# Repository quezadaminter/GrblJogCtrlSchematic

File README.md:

# GrblJogCtrlSchematic
Schematic for the embedded GRBL jog controller.  

This is in the form of a KiCAD project.  

The microcontroller board used (Teensy 4.1): https://www.pjrc.com/store/teensy41.html  

The Display breakout board called out in the schematic can be ordered from OshPark: https://oshpark.com/shared_projects/ZNeN5t92  
The TFT LCD I used is from BuyDisplay.com: https://www.buydisplay.com/serial-spi-3-5-inch-tft-lcd-module-in-320x480-optl-touchscreen-ili9488  

I have no affiliation with BuyDislay.com or PJRC.  

Write up about the device with pictures and links to demo videos: https://discuss.inventables.com/t/grbl-hand-held-controller-with-jog-wheel-dro-and-built-in-sender/109009  

Source code for the Teensy 4.1: https://github.com/quezadaminter/GrblJogCtrl  

# Page 1/3

# Page 2/3

# Page 3/3

# Parts Used
1- Teensy 4.1 Development Board.  
1- ILI9488 LCD https://www.buydisplay.com/serial-spi-3-5-inch-tft-lcd-module-in-320x480-optl-touchscreen-ili9488  
1- 50 pin LCD breakout adapter board. Link in the schematic.  
1- 12 Button key pad, I made my own but there are many options out there.  
1- Shift register IC to read keypad.  
2- 12 position rotary selector switches (12PST).  
1- Female USB 2.0 type A connector.  
1- 20 pulse rotary encoder with momentary switch. Feel free to substitute for one with a higher resolution.

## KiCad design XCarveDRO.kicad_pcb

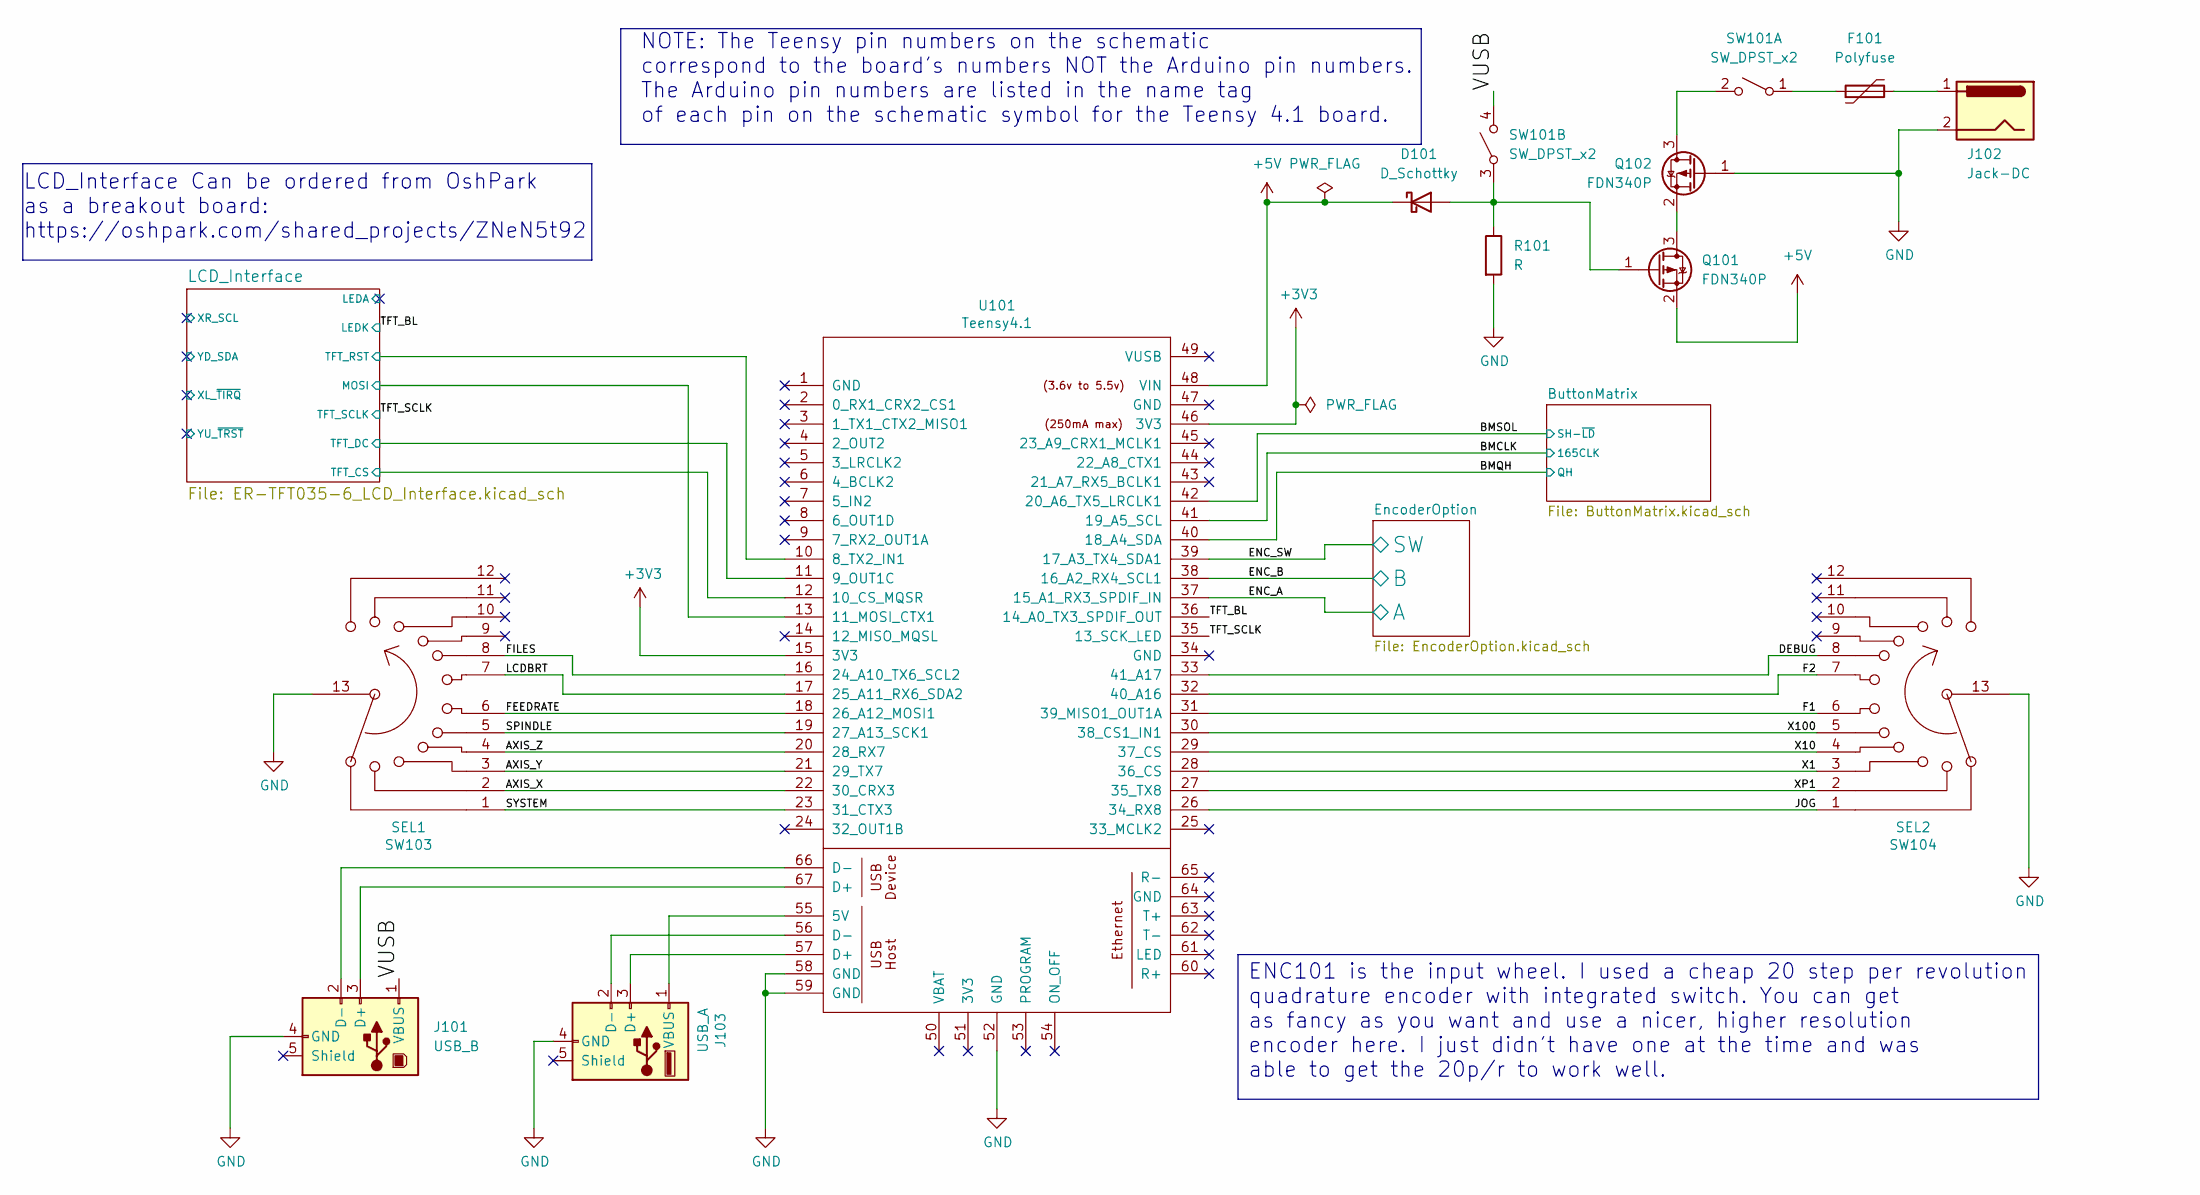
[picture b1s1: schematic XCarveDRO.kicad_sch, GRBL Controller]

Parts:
D101: D_Schottky; D_SOD-323_HandSoldering
F101: Polyfuse; Fuse_1210_3225Metric_Pad1.42x2.65mm_HandSolder
J101: USB_B; USB_B_Lumberg_2411_02_Horizontal
J102: Jack-DC; PinHeader_1x02_P2.54mm_Vertical
J103: USB_A; USB_A_Stewart_SS-52100-001_Horizontal
Q101, Q102: FDN340P; SOT-23
R101: R; R_0805_2012Metric_Pad1.20x1.40mm_HandSolder
SW101: SW_DPST_x2; PinHeader_1x04_P2.54mm_Vertical
SW103: SEL1; SWITCH_ROTARY_4-12-No_Cuts
SW104: SEL2; SWITCH_ROTARY_4-12-No_Cuts
U101: Teensy4.1; Teensy41

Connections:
+5V: D101.1 (K), Q101.2 (S), U101.48 (VIN)
/AXIS_X: SW103.2, U101.22 (30_CRX3)
/AXIS_Y: SW103.3, U101.21 (29_TX7)
/AXIS_Z: SW103.4, U101.20 (28_RX7)
/BMCLK: U101.41 (19_A5_SCL); also elsewhere on the board
/BMQH: U101.40 (18_A4_SDA); also elsewhere on the board
/BMSOL: U101.42 (20_A6_TX5_LRCLK1); also elsewhere on the board
/DEBUG: SW104.8, U101.33 (41_A17)
/ENC_A: U101.37 (15_A1_RX3_SPDIF_IN); also elsewhere on the board
/ENC_B: U101.38 (16_A2_RX4_SCL1); also elsewhere on the board
/ENC_SW: U101.39 (17_A3_TX4_SDA1); also elsewhere on the board
/F1: SW104.6, U101.31 (39_MISO1_OUT1A)
/F2: SW104.7, U101.32 (40_A16)
/FEEDRATE: SW103.6, U101.18 (26_A12_MOSI1)
/FILES: SW103.8, U101.16 (24_A10_TX6_SCL2)
/JOG: SW104.1, U101.26 (34_RX8)
/LCDBRT: SW103.7, U101.17 (25_A11_RX6_SDA2)
/LCD_Interface/MOSI: U101.13 (11_MOSI_CTX1); also elsewhere on the board
/LCD_Interface/TFT_CS: U101.12 (10_CS_MQSR); also elsewhere on the board
/LCD_Interface/TFT_DC: U101.11 (9_OUT1C); also elsewhere on the board
/LCD_Interface/TFT_RST: U101.10 (8_TX2_IN1); also elsewhere on the board
/SPINDLE: SW103.5, U101.19 (27_A13_SCK1)
/SYSTEM: SW103.1, U101.23 (31_CTX3)
/TFT_BL: U101.36 (14_A0_TX3_SPDIF_OUT); also elsewhere on the board
/TFT_SCLK: U101.35 (13_SCK_LED); also elsewhere on the board
/VUSB: J101.1 (VBUS), SW101.4 (B)
/X1: SW104.3, U101.28 (36_CS)
/X10: SW104.4, U101.29 (37_CS)
/X100: SW104.5, U101.30 (38_CS1_IN1)
/XP1: SW104.2, U101.27 (35_TX8)
GND: J101.4 (GND), J102.2, J103.4 (GND), Q102.1 (G), R101.2, SW103.13, SW104.13, U101.52 (GND), U101.58 (GND), U101.59 (GND); also elsewhere on the board
unnamed: D101.2 (A), Q101.1 (G), R101.1, SW101.3 (A)
unnamed: F101.1, SW101.1 (A)
unnamed: F101.2, J102.1
unnamed: J101.2 (D-), U101.66 (D-)
unnamed: J101.3 (D+), U101.67 (D+)
unnamed: J103.1 (VBUS), U101.55 (5V)
unnamed: J103.2 (D-), U101.56 (D-)
unnamed: J103.3 (D+), U101.57 (D+)
unnamed: Q101.3 (D), Q102.2 (S)
unnamed: Q102.3 (D), SW101.2 (B)

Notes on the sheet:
LCD_Interface Can be ordered from OshPark as a breakout board: https://oshpark.com/shared_projects/ZNeN5t92
NOTE: The Teensy pin numbers on the schematic correspond to the board's numbers NOT the Arduino pin numbers. The Arduino pin numbers are listed in the name tag of each pin on the schematic symbol for the Teensy 4.1 board.
ENC101 is the input wheel. I used a cheap 20 step per revolution quadrature encoder with integrated switch. You can get as fancy as you want and use a nicer, higher resolution encoder here. I just didn't have one at the time and was able to get the 20p/r to work well.

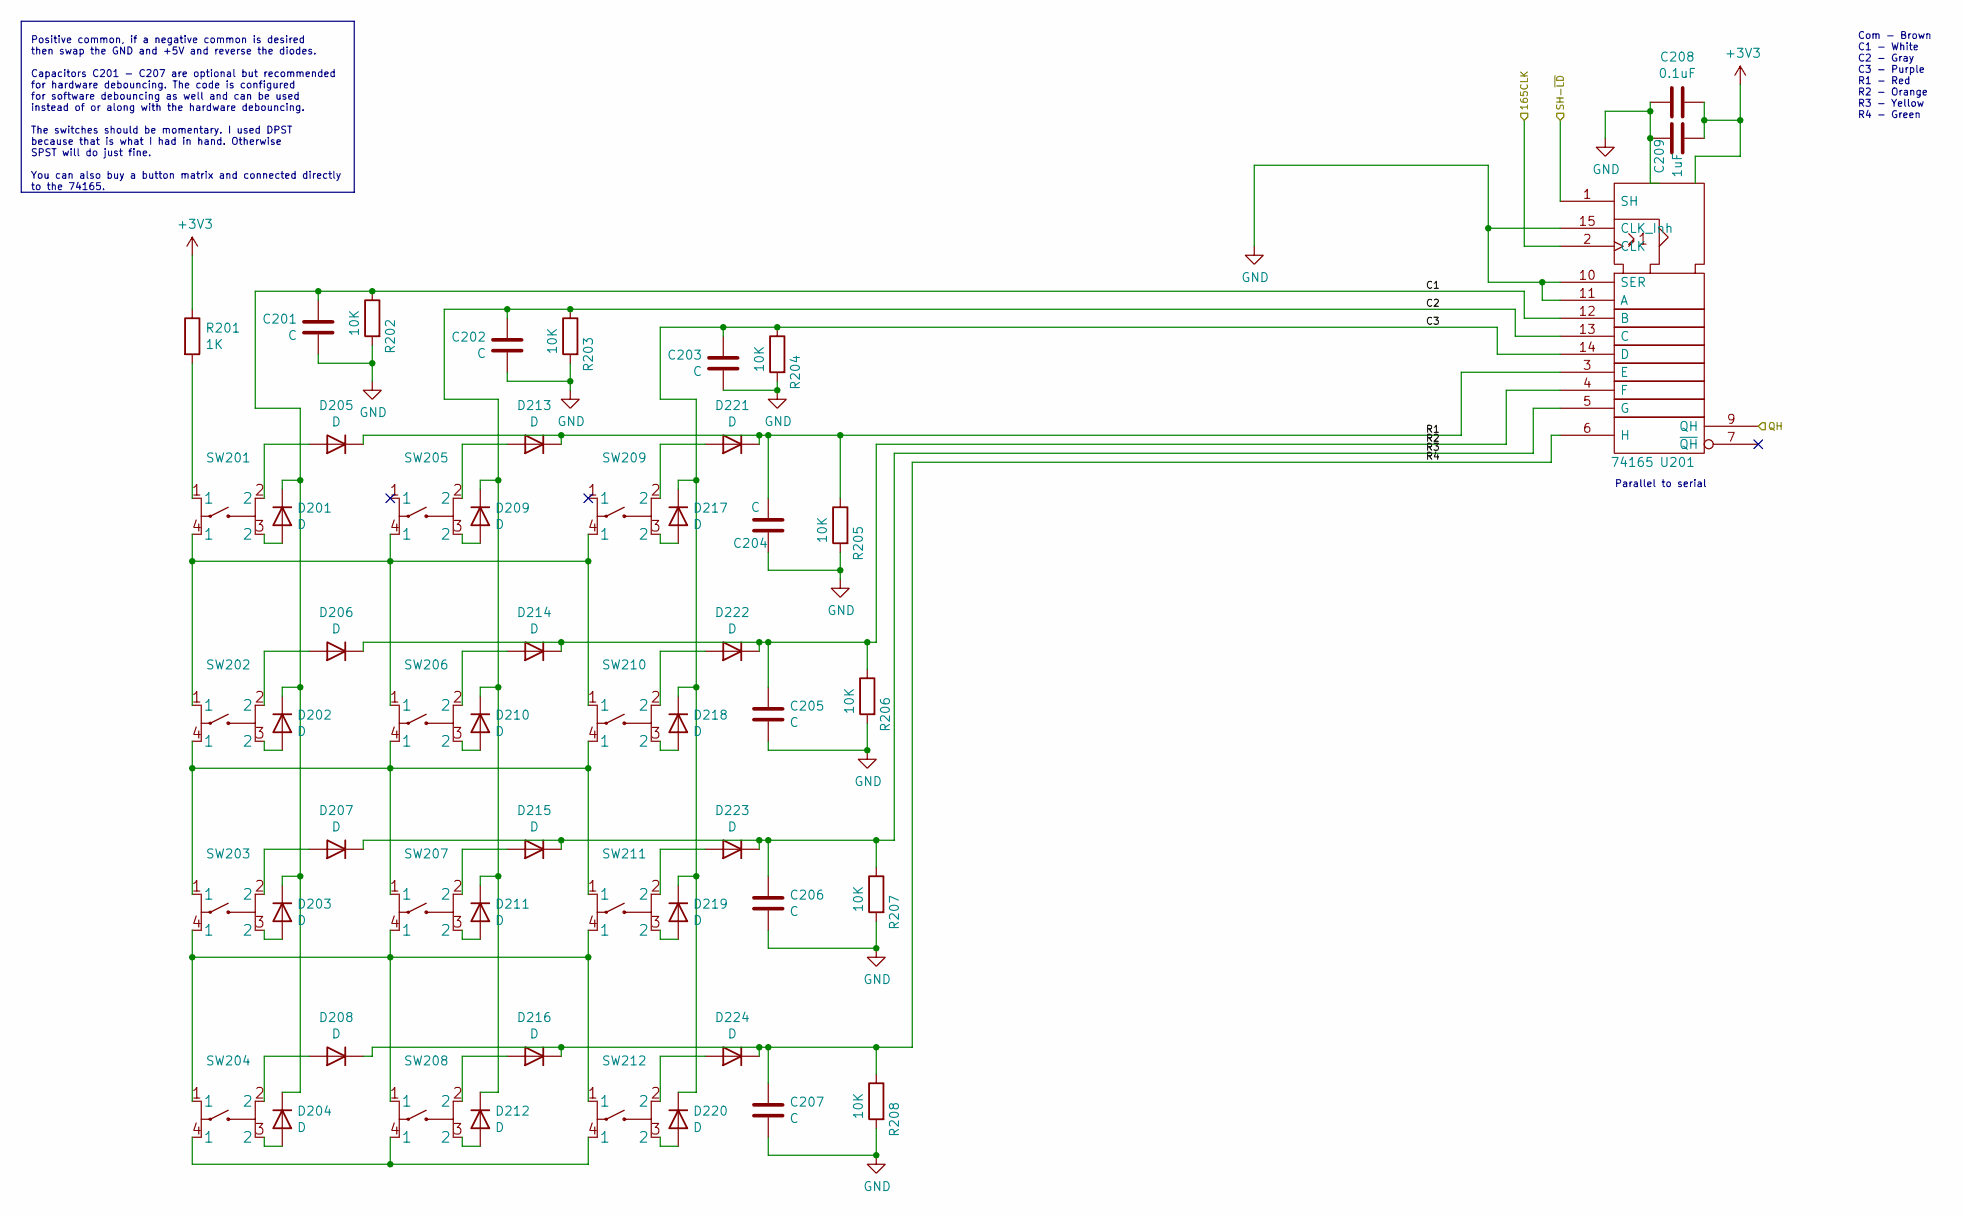
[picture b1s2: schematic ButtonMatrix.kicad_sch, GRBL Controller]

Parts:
C201, C202, C203, C204, C205, C206, C207: C; C_0805_2012Metric_Pad1.18x1.45mm_HandSolder
C208: 0.1uF; C_0805_2012Metric_Pad1.18x1.45mm_HandSolder
C209: 1uF; C_0805_2012Metric_Pad1.18x1.45mm_HandSolder
D201, D202, D203, D204, D205, D206, D207, D208, D209, D210, D211, D212, D213, D214, D215, D216, D217, D218, D219, D220, D221, D222, D223, D224: D; D_SOD-323_HandSoldering
R201: 1K; R_0805_2012Metric_Pad1.20x1.40mm_HandSolder
R202, R203, R204, R205, R206, R207, R208: 10K; R_0805_2012Metric_Pad1.20x1.40mm_HandSolder
SW201, SW202, SW203, SW204, SW205, SW206, SW207, SW208, SW209, SW210, SW211, SW212: FSM4JSMATR
U201: 74165; DIP-16_W7.62mm_LongPads

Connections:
/BMCLK: U201.2 (CLK); also elsewhere on the board
/BMQH: U201.9 (QH); also elsewhere on the board
/BMSOL: U201.1 (SH); also elsewhere on the board
/ButtonMatrix/C1: C201.2, D201.1 (K), D202.1 (K), D203.1 (K), D204.1 (K), R202.1, U201.12 (B)
/ButtonMatrix/C2: C202.2, D209.1 (K), D210.1 (K), D211.1 (K), D212.1 (K), R203.1, U201.13 (C)
/ButtonMatrix/C3: C203.2, D217.1 (K), D218.1 (K), D219.1 (K), D220.1 (K), R204.1, U201.14 (D)
/ButtonMatrix/R1: C204.1, D205.1 (K), D213.1 (K), D221.1 (K), R205.1, U201.3 (E)
/ButtonMatrix/R2: C205.1, D206.1 (K), D214.1 (K), D222.1 (K), R206.1, U201.4 (F)
/ButtonMatrix/R3: C206.1, D207.1 (K), D215.1 (K), D223.1 (K), R207.1, U201.5 (G)
/ButtonMatrix/R4: C207.1, D208.1 (K), D216.1 (K), D224.1 (K), R208.1, U201.6 (H)
GND: C201.1, C202.1, C203.1, C204.2, C205.2, C206.2, C207.2, C208.2, C209.2, R202.2, R203.2, R204.2, R205.2, R206.2, R207.2, R208.2, U201.8 (GND), U201.10 (SER), U201.11 (A), U201.15 (CLK_Inh); also elsewhere on the board
unnamed: D201.2 (A), SW201.3 (2)
unnamed: D202.2 (A), SW202.3 (2)
unnamed: D203.2 (A), SW203.3 (2)
unnamed: D204.2 (A), SW204.3 (2)
unnamed: D205.2 (A), SW201.2
unnamed: D206.2 (A), SW202.2
unnamed: D207.2 (A), SW203.2
unnamed: D208.2 (A), SW204.2
unnamed: D209.2 (A), SW205.3 (2)
unnamed: D210.2 (A), SW206.3 (2)
unnamed: D211.2 (A), SW207.3 (2)
unnamed: D212.2 (A), SW208.3 (2)
unnamed: D213.2 (A), SW205.2
unnamed: D214.2 (A), SW206.2
unnamed: D215.2 (A), SW207.2
unnamed: D216.2 (A), SW208.2
unnamed: D217.2 (A), SW209.3 (2)
unnamed: D218.2 (A), SW210.3 (2)
unnamed: D219.2 (A), SW211.3 (2)
unnamed: D220.2 (A), SW212.3 (2)
unnamed: D221.2 (A), SW209.2
unnamed: D222.2 (A), SW210.2
unnamed: D223.2 (A), SW211.2
unnamed: D224.2 (A), SW212.2
unnamed: R201.2, SW201.1
unnamed: SW201.4 (1), SW202.1, SW205.4 (1), SW206.1, SW209.4 (1), SW210.1
unnamed: SW202.4 (1), SW203.1, SW206.4 (1), SW207.1, SW210.4 (1), SW211.1
unnamed: SW203.4 (1), SW204.1, SW207.4 (1), SW208.1, SW211.4 (1), SW212.1
unnamed: SW204.4 (1), SW208.4 (1), SW212.4 (1)

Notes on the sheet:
Parallel to serial
Com - Brown C1 - White C2 - Gray C3 - Purple R1 - Red R2 - Orange R3 - Yellow R4 - Green
Positive common, if a negative common is desired then swap the GND and +5V and reverse the diodes. Capacitors C201 - C207 are optional but recommended for hardware debouncing. The code is configured for software debouncing as well and can be used instead of or along with the hardware debouncing. Th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

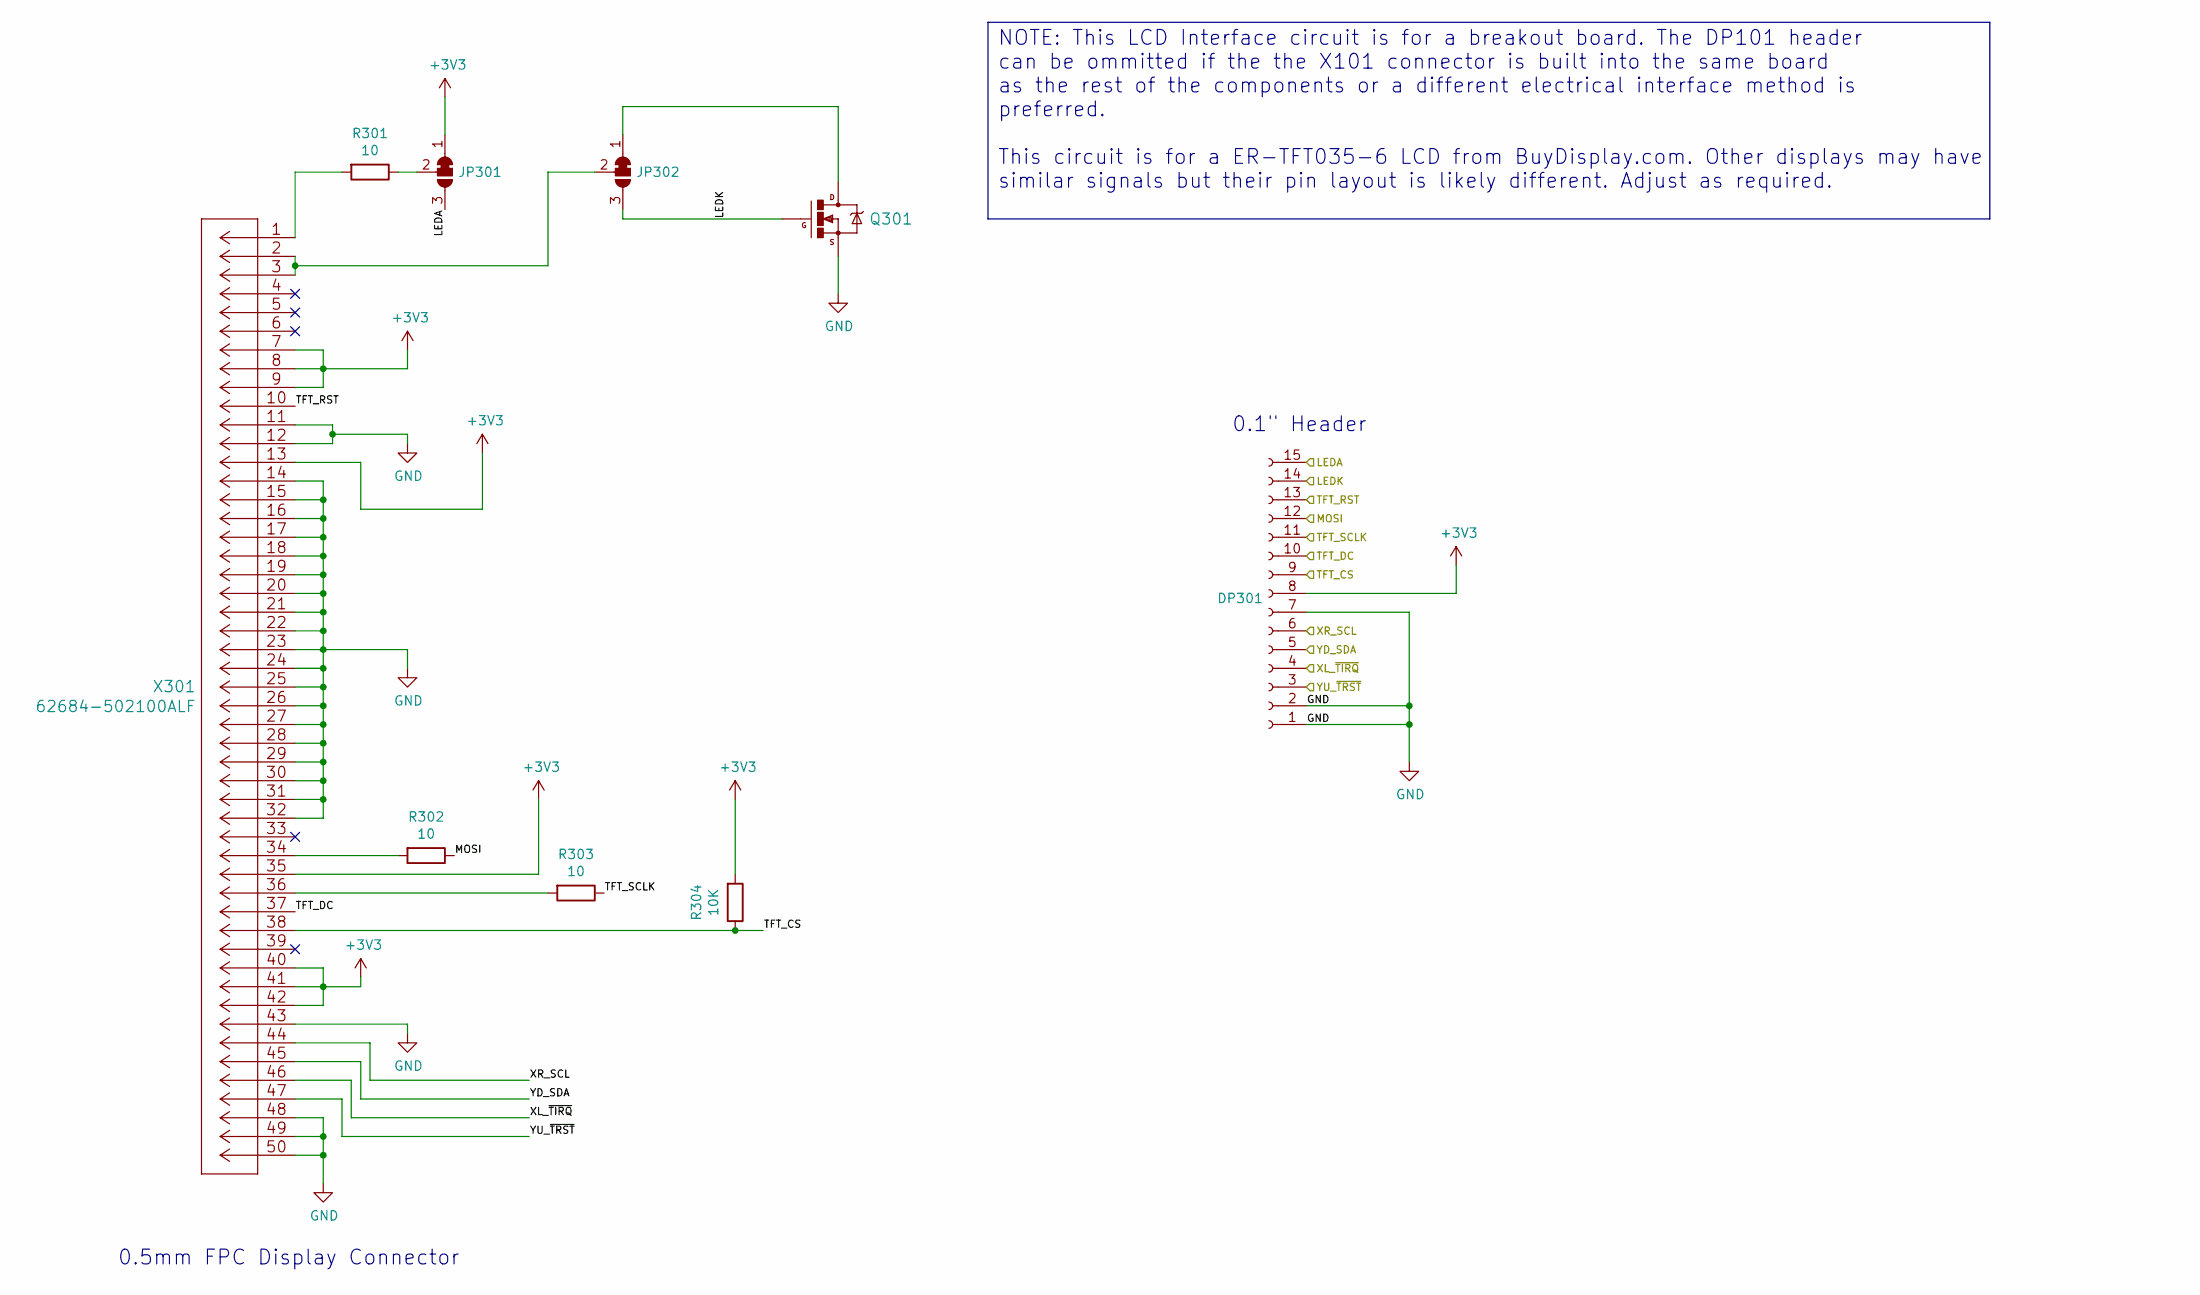
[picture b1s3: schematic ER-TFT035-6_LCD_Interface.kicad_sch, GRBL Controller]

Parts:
DP301: Conn_01x15_Female; PinSocket_1x15_P2.54mm_Vertical
JP301, JP302: SolderJumper_3_Bridged12; SolderJumper-3_P2.0mm_Open_TrianglePad1.0x1.5mm_NumberLabels
Q301: IRLML0040TR; SOT-23
R301, R302, R303: 10; R_0805_2012Metric_Pad1.20x1.40mm_HandSolder
R304: 10K; R_0805_2012Metric_Pad1.20x1.40mm_HandSolder
X301: 62684-502100ALF; TFT_3.5IN_320X480_50PIN_BUY_DISPLAY_ER-TFT035-6

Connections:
/LCD_Interface/LEDA: JP301.3 (B)
/LCD_Interface/MOSI: R302.1; also elsewhere on the board
/LCD_Interface/TFT_CS: R304.1, X301.38; also elsewhere on the board
/LCD_Interface/TFT_DC: X301.37; also elsewhere on the board
/LCD_Interface/TFT_RST: X301.10; also elsewhere on the board
/LCD_Interface/XL_~TIRQ: X301.46
/LCD_Interface/XR_SCL: X301.44
/LCD_Interface/YD_SDA: X301.45
/LCD_Interface/YU_~TRST: X301.47
/TFT_BL: JP302.3 (B), Q301.1 (G); also elsewhere on the board
/TFT_SCLK: R303.1; also elsewhere on the board
GND: DP301.1, DP301.2, DP301.7, Q301.2 (S), X301.11, X301.12, X301.14, X301.15, X301.16, X301.17, X301.18, X301.19, X301.20, X301.21, X301.22, X301.23, X301.24, X301.25, X301.26, X301.27, X301.28, X301.29, X301.30, X301.31, X301.32, X301.43, X301.48, X301.49, X301.50; also elsewhere on the board
unnamed: JP301.2 (C), R301.1
unnamed: JP302.1 (A), Q301.3 (D)
unnamed: JP302.2 (C), X301.2, X301.3
unnamed: R301.2, X301.1
unnamed: R302.2, X301.34
unnamed: R303.2, X301.36

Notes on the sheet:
0.1" Header
NOTE: This LCD Interface circuit is for a breakout board. The DP101 header can be ommitted if the the X101 connector is built into the same board as the rest of the components or a different electrical interface method is preferred. This circuit is for a ER-TFT035-6 LCD from BuyDisplay.com. Other d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
0.5mm FPC Display Connector

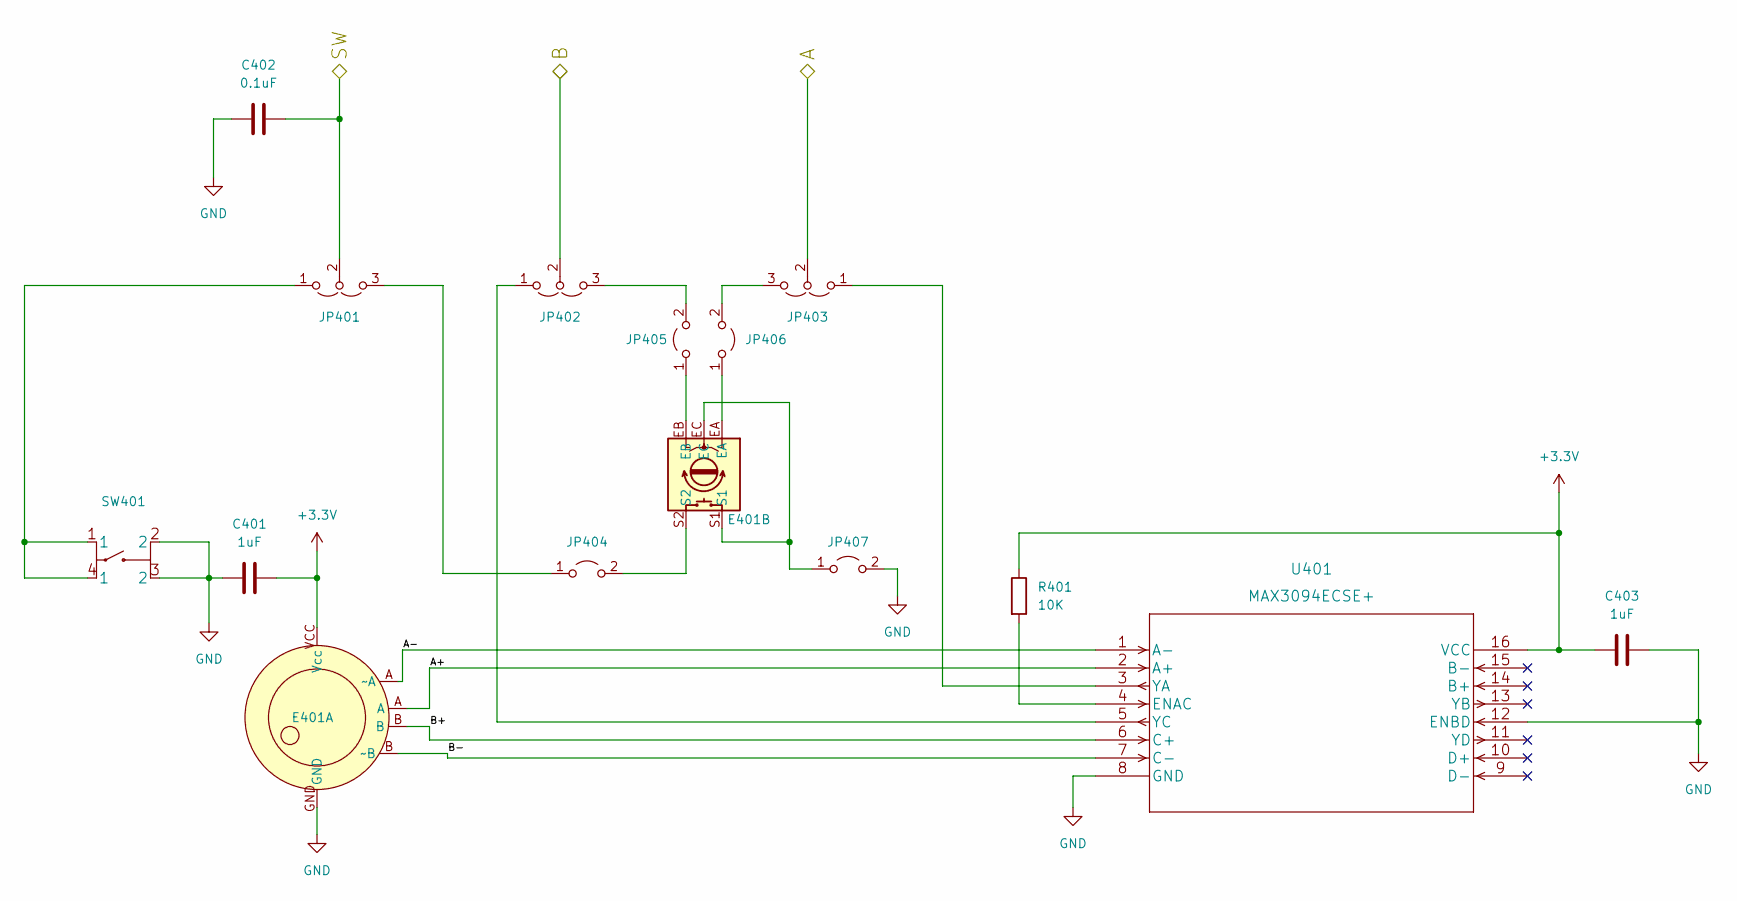
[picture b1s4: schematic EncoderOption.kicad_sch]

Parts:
C401, C403: 1uF; C_0805_2012Metric_Pad1.18x1.45mm_HandSolder
C402: 0.1uF; C_0805_2012Metric_Pad1.18x1.45mm_HandSolder
E401: Combined_MPG_ENCODER; HAND_WHEEL_ENCODER
JP401, JP402, JP403: Jumper_3_Open; SolderJumper-3_P2.0mm_Open_TrianglePad1.0x1.5mm_NumberLabels
JP404, JP405, JP406, JP407: Jumper_2_Open; SolderJumper-2_P-1mm-Gap_Open_RoundedPad1.0x1.5mm
R401: 10K; R_0805_2012Metric_Pad1.20x1.40mm_HandSolder
SW401: FSM4JSMATR
U401: MAX3094ECSE+; SOIC-16_3.9x9.9mm_P1.27mm

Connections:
/ENC_A: JP403.2 (C); also elsewhere on the board
/ENC_B: JP402.2 (C); also elsewhere on the board
/ENC_SW: C402.2, JP401.2 (C); also elsewhere on the board
/EncoderOption/A+: E401.A, U401.2 (A+)
/EncoderOption/A-: E401.~A, U401.1 (A-)
/EncoderOption/B+: E401.B, U401.6 (C+)
/EncoderOption/B-: E401.~B, U401.7 (C-)
GND: C401.2, C402.1, C403.2, E401.GND, JP407.2 (B), SW401.2, SW401.3 (2), U401.8 (GND), U401.12 (ENBD); also elsewhere on the board
unnamed: E401.EA, JP406.1 (A)
unnamed: E401.EB, JP405.1 (A)
unnamed: E401.EC, E401.S1, JP407.1 (A)
unnamed: E401.S2, JP404.2 (B)
unnamed: JP401.1 (A), SW401.1, SW401.4 (1)
unnamed: JP401.3 (B), JP404.1 (A)
unnamed: JP402.1 (A), U401.5 (YC)
unnamed: JP402.3 (B), JP405.2 (B)
unnamed: JP403.1 (A), U401.3 (YA)
unnamed: JP403.3 (B), JP406.2 (B)
unnamed: R401.2, U401.4 (ENAC)

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
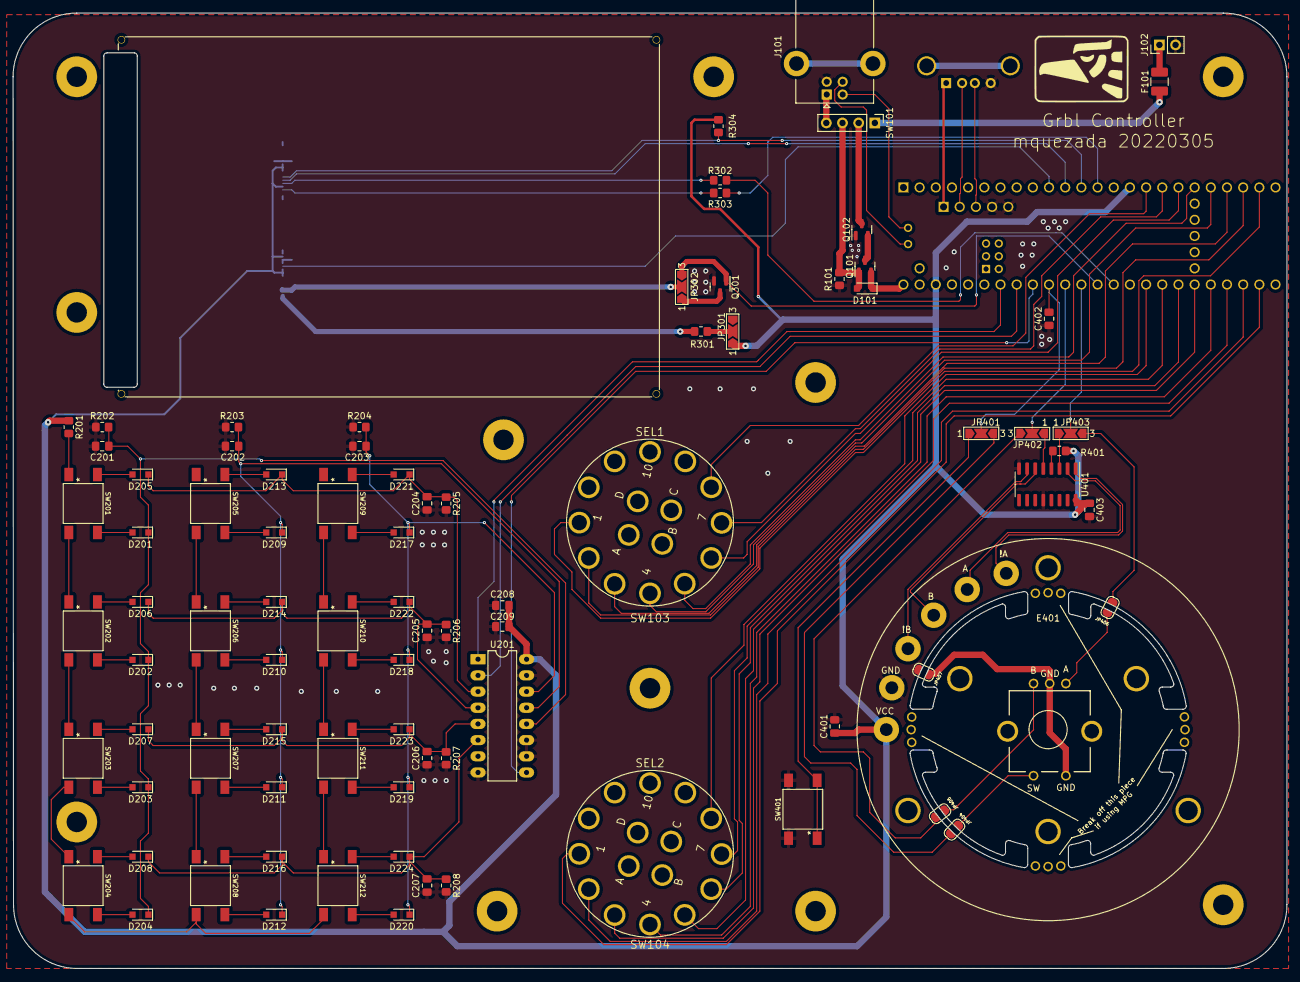
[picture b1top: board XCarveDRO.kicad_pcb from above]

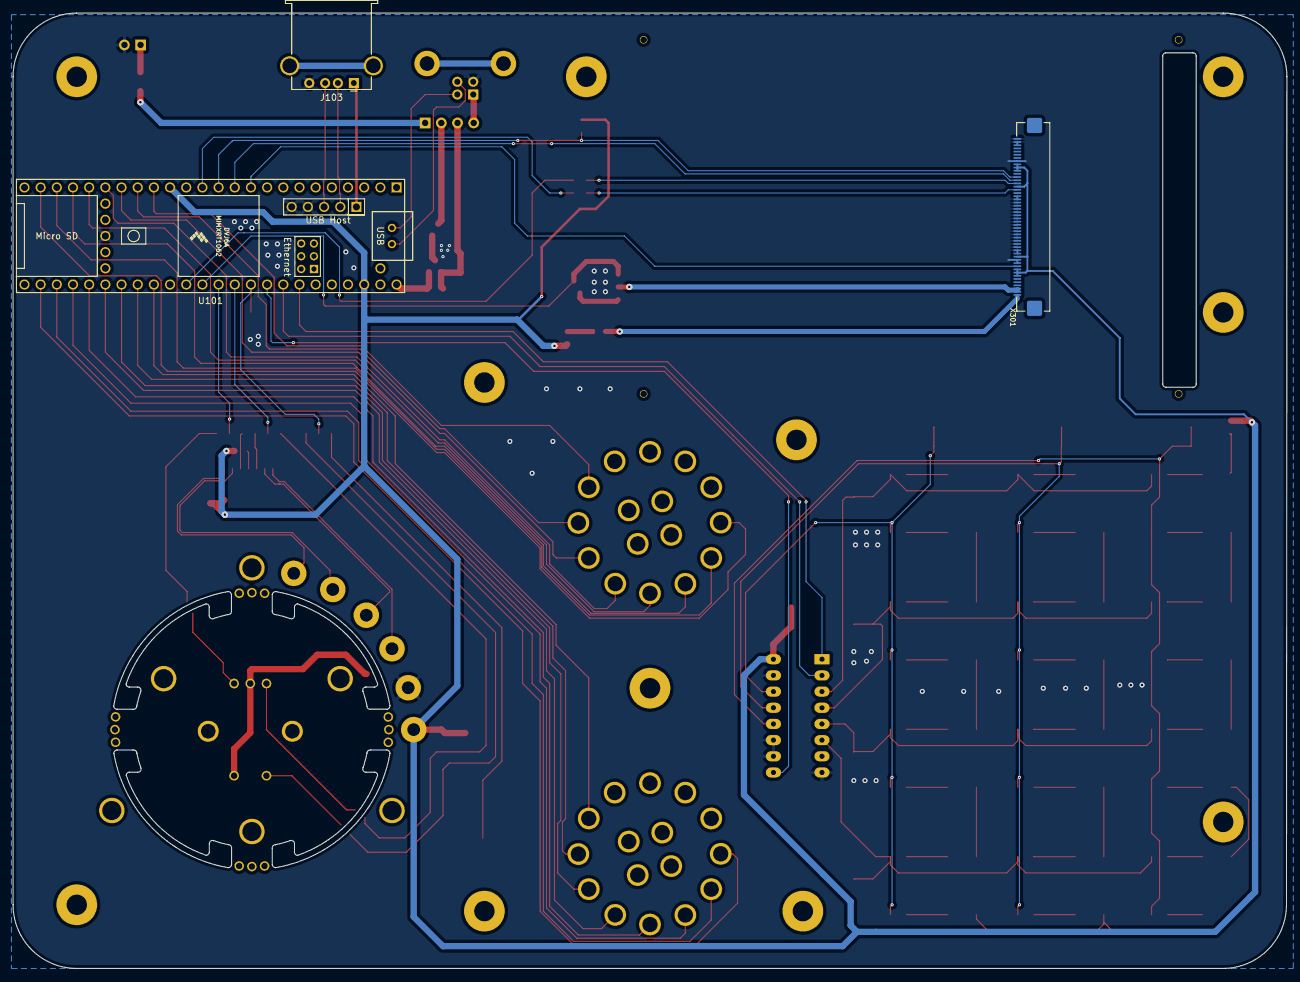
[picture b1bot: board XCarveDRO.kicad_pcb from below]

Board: 2 copper layers, 200.0 x 150.0 mm, 88 parts (2 on the bottom side), 99 nets.

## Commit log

2021-01-10 Initial commit with schematic only.
2021-01-10 Create SVG files of the schematic so folks don't have to use KiCAD to view it.
2021-01-10 Add SVG of schematics.
2021-01-10 Create LICENSE
2022-01-05 Use new link for TFT breakout board on OshPark.
2022-01-05 Based on feedback, update silkscreen on DP101 and link to OSHPark, R201 from 10K to 1K.
2022-01-11 Update schematic to use the oshpark board layout so there is more consistency between the two. Update notes descriptions and bump to revision 1.
2022-02-06 Migrate files to kicad v6.
2022-02-07 Move encoder into its own sheet. Replace with MPG/Encoder combo.
2022-03-05 Added the MPG. Switched tactile button model. Added JLC design rules.
2022-11-08 Update 3D components.
